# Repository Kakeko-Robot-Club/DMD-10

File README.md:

# DMD-10
ディスクリート部品によるDCブラシモータドライバ
## 目次
 - [仕様](#仕様)
 - [変更履歴](#変更履歴)
 - [発注](#発注)
 - [部品実装](#部品実装)
 - [使い方](#使い方)
## 仕様
### 絶対最大定格
| 項目                  | 記号            | Max      | 単位 | 
| --------------------- | :-------------: | :------: | :--: | 
| モータ出力電流(rms)   | I<sub>OUT</sub>      | 10       | A    | 
| モータ出力電流(peak)  | I<sub>OUT_PEAK</sub> | 17       | A    | 
| モータ電源電圧        | V<sub>DD</sub>       | 0~16     | V    | 
| ロジック入力電圧      | V<sub>IN</sub>       | -6~23    | V    | 
| 保存温度             | T<sub>S</sub>      | -55~125   | ℃   | 
### 電気的特性・動作範囲
| 項目                  | 記号            | Min | Typ. | Max | 単位 | コンディション    | 
| --------------------- | :-------------: | :-: | :--: | :-: | :--: | ----------------- | 
| モータ電源電圧        | V<sub>DD</sub>  | 6   | -    | 16  | V    |                   | 
| ロジック入力電圧(High)| V<sub>IH</sub>  | 3.6 | -    | 20  | V    |                   | 
| ロジック入力電圧(Low) | V<sub>IL</sub>  | 0   | -    | 1.4 | V    |                   | 
| ロジックPWM周波数    | f<sub>IN</sub>  | -   | -    | 27  | kHz    |                   | 
| ロジック入力電流      | I<sub>IN</sub>  | -   | 10   | -   | mA   | V<sub>IN</sub>=5V | 
### その他
| 項目                  | 記号            | Min | Typ. | Max | 単位 | 備考              | 
| --------------------- | :-------------: | :-: | :--: | :-: | :--: | ----------------- | 
| 基板サイズ(縦)        |                 | -   | 55   | -   | mm   |                   | 
| 基板サイズ(横)        |                 | -   | 60   | -   | mm   |                   | 
| 取り付け穴サイズ      |                 | -   | 3.2  | -   | mm   | M3ネジ用          | 
| 取り付け穴ピッチ(縦)  |                 | -   | 46   | -   | mm   |                   | 
| 取り付け穴ピッチ(横)  |                 | -   | 35   | -   | mm   |                   | 
### 図
 - [回路図](https://github.com/Kakeko-Robot-Club/DMD-10/blob/main/preview/schematic.pdf)
 - [基板外形図](https://github.com/Kakeko-Robot-Club/DMD-10/blob/main/preview/pcb.pdf)
## 変更履歴
 - Rev. A
	 - 初版(GitHubには未掲載)
 - Rev. B
	 - 部品リファレンス番号の振り直し
## 発注
 - 発注手順は[Elecrow](https://www.elecrow.com/pcb-manufacturing.html)に発注する際の手順を示しているため、その他の業者に発注する際は各業者の指示に従うこと。
 - 下の1～4の手順が難しい場合、このリポジトリの中にあるgerberフォルダの中のファイルを使用しても良い。ただし、手順1が行えないため注意。
 - 設定はKiCad v5系を元にしているため、その他のバージョンの場合は同等の設定にすること。
1. KiCadのPcbnewを用いて基板型番の下にある週番号を振り直す。
	 - この手順は省略できるが、製造時期を明確にするために行ったほうが良い。
2. Pcbnewから、ファイル→プロットと進み、出てきた画面で次のように設定をし、「製造ファイル出力」を押す。
	 - 出力フォーマット: ガーバー
	 - 出力ディレクトリ: gerberなど分かりやすいもの
	 - 含まれるレイヤ
		 - [x] F.Cu
		 - [x] B.Cu
		 - [x] F.SilkS
		 - [x] B.SilkS
		 - [x] F.Mask
		 - [x] B.Mask
		 - [x] Edge.Cuts
		 - その他はチェックを外す
	 - 全般オプション
		 - [x] フットプリントの定数をプロット
		 - [x] フットプリントのリファレンスをプロット
		 - [x] 基板外形レイヤーのデータを他のレイヤーから除外
		 - [x] シルクからパッドを除外
		 - その他はチェックを外す
		 - デフォルトの線幅: 0.1mm
	 - ガーバーオプション
		 - [x] Protelの拡張子を使用
		 - [x] シルクをレジストで抜く
		 - [x] ネットリスト属性を含む
		 - その他はチェックを外す
		 - 座標フォーマット: 4.6, 単位 mm
3. 製造ファイル出力ボタンの右の方にある、「ドリルファイルを生成...」ボタンから、次のように設定し、「ドリルファイルを生成」を押す。
	 - 出力フォルダ: 製造ファイル出力で設定したものと同じもの
	 - ドリルファイルフォーマット: Excellon
		 - チェックはすべて外す
		 - 長円穴ドリルモードは「routeコマンドを使用」にチェック
	 - マップファイルフォーマット: ガーバー
	 - ドリル原点: 絶対位置
	 - ドリル単位: mm
	 - ゼロの扱い: 後方ゼロ省略
4. 基板プロジェクトフォルダの中のフォルダ、または自分で設定したフォルダの中に生成したファイル群があるので、次のようにリネームする。
	 - DMD-10-Edge.Cuts.gm1のみ、拡張子がgmlに変わっているため注意

	| 元ファイル名         | リネーム後      | 
	| -------------------- | --------------- | 
	| DMD-10-B.Cu.gbl      | DMD-10.gbl      | 
	| DMD-10-B.Mask.gbs    | DMD-10.gbs      | 
	| DMD-10-B.SilkS.gbo   | DMD-10.gbo      | 
	| DMD-10-Edge.Cuts.gm1 | DMD-10.gml      | 
	| DMD-10-F.Cu.gtl      | DMD-10.gtl      | 
	| DMD-10-F.Mask.gts    | DMD-10.gts      | 
	| DMD-10-F.SilkS.gto   | DMD-10.gto      | 
	| DMD-10-NPTH.drl      | DMD-10-NPTH.txt | 
	| DMD-10-PTH.drl       | DMD-10-PTH.txt  | 
5. ファイルをZIPファイルに圧縮する。
6. [Elecrow](https://www.elecrow.com/pcb-manufacturing.html)にZIPファイルをアップロードし、次のような設定で発注する。
	 - Elecrowにログインしておくこと。

	| 項目                 | 設定             | 備考                                                   | 
	| -------------------- | :--------------: | ------------------------------------------------------ | 
	| Layer                | 2 layers         | 変更しないこと。                                       | 
	| Dimensions           | 60 x 55          | 変更しないこと。                                       | 
	| PCB Qty              | 必要枚数を設定   | 10枚までは安い。設定より少し多めに届くことが多い。     | 
	| Different PCB Design | 1                | 変更しないこと。                                       | 
	| PCB Thickness        | 1.6              | 薄くできるが非推奨。厚くすると高くなる。               | 
	| PCB Color            | 基板色を設定     | 一部の色は高い。                                       | 
	| Surface Finish       | HASL             | 鉛フリーや金メッキなども指定できるが高くなる。         | 
	| Castellated Hole     | No               | 変更しないこと。                                       | 
	| Copper Weight        | 1oz              | 2ozは基板銅箔が厚くなるが高くなる。                    | 
	| PCB Stencil          | No               | ステンシルは表面実装部品のリフロー半田に使うので不要。 | 
	| Production Time      | 4-7 working days | Rushなどにしてもそこまで早くならない。                 | 
	| Country              | Japan            | 配送先の国なので日本を選択。                           | 
	| Shipping Cost        | Sagawa           | 一番安いものを選んでおけばよい。                       | 
## 部品実装
 - 部品リスト
	| リファレンス | 部品                | 秋月電子                                                                                                                        | 代替品情報                                              | 
	| ------------ | ------------------- | ------------------------------------------------------------------------------------------------------------------------------- | ------------------------------------------------------- | 
	| D1～D4       | SBM1045VSS          | [I-15642](https://akizukidenshi.com/catalog/g/gI-15642/)                                                                        | I<sub>F</sub>>10A, V<sub>R</sub>>16V                    | 
	| J1～J4       | PCB-20(632F)        | [C-05115](https://akizukidenshi.com/catalog/g/gC-05115/)                                                                        | 15A以上流せるもの, できるだけ金属面積が広いもの         | 
	| J5           | PH-1x40RG(2)        | [C-01627](https://akizukidenshi.com/catalog/g/gC-01627/)                                                                        | 2.54mmピッチ, L字                                       | 
	| Q1, Q2       | MTA100N10KRI3       | 1個: [I-15846](https://akizukidenshi.com/catalog/g/gI-15846/)<br>10個: [I-15847](https://akizukidenshi.com/catalog/g/gI-15847/) | TO-251, Nch, I<sub>D</sub>>2A, V<sub>GS(th)</sub><4V    | 
	| Q3, Q5       | IRFU5505PBF         | [I-06021](https://akizukidenshi.com/catalog/g/gI-06021/)                                                                        | TO-251, Pch, I<sub>D</sub><-15A, V<sub>GS(th)</sub>>-4V | 
	| Q4, Q6       | IRLU3410PBF         | [I-06025](https://akizukidenshi.com/catalog/g/gI-06025/)                                                                        | TO-251, Nch, I<sub>D</sub>>15A, V<sub>GS(th)</sub><4V   | 
	| R1～R4       | 300Ωカーボン抵抗   | [R-07811](https://akizukidenshi.com/catalog/g/gR-07811/)                                                                        |                                                         | 
	| R5, R6       | 10kΩカーボン抵抗   | [R-07838](https://akizukidenshi.com/catalog/g/gR-07838/)                                                                        |                                                         | 
	| R7～R10      | 10Ωカーボン抵抗    | [R-07795](https://akizukidenshi.com/catalog/g/gR-07795/)                                                                        |                                                         | 
	| RN1          | 1kΩ 4素子集合抵抗  | [R-14225](https://akizukidenshi.com/catalog/g/gR-14225/)                                                                        |                                                         | 
	| RN2          | 10kΩ 4素子集合抵抗 | [R-11909](https://akizukidenshi.com/catalog/g/gR-11909/)                                                                        |                                                         | 
	| U1, U2       | UPC817CG-D04-T      | [I-16090](https://akizukidenshi.com/catalog/g/gI-16090/)                                                                        | PC817系フォトカプラ                                     | 
 - 注意点
	 - 抵抗やダイオードは縦取り付けになるよう、リードを曲げること。
	 - リードを曲げた抵抗を取り付ける際、基板から浮かないように取り付けること。
		 - 浮いている場合、抵抗が左右に曲がりやすくなり、ショートの原因になるため注意。
	 - 放熱のため、FETの頭の部分の半田付けは確実に行う。
		 - ランドが広いため、大出力の半田ごてを用いたほうが良い。
	 - ネジ端子はよく温めないと半田が流れないため、やけどに注意。
	 - 言うまでもなく、部品の向き・極性の間違い、定数の間違いに注意する。
## 使い方
1. 次のように接続する。
	| 端子      | リファレンス | 接続先             | 
	| --------- | ------------ | ------------------ | 
	| POWER IN  | J2           | モータ電源プラス   | 
	| POWER GND | J3           | モータ電源マイナス | 
	| MOTOR OUT | J1, J4       | DCブラシモータ     | 
	| IN1       | J5           | マイコン等出力端子 | 
	| IN2       | J5           | マイコン等出力端子 | 
	| GND       | J5           | マイコン等グランド | 
2. マイコン等から次の表に従い、IN1・IN2に信号を出力する。
	| IN2 | IN1 | J4  | J1  | モータ   | 
	| --- | --- | --- | --- | -------- | 
	| 0   | 0   | 1   | 1   | ブレーキ | 
	| 0   | 1   | 1   | 0   | 回転     | 
	| 1   | 0   | 0   | 1   | 逆回転   | 
	| 1   | 1   | 0   | 0   | ブレーキ | 
  
	*IN1・IN2欄は入力状態、J1・J4欄は出力状態、モータ欄は出力状態によるモータの状態を表す。  
	*IN1・IN2については0をV<sub>IL</sub>、1をV<sub>IH</sub>（PWM入力含む）に従うものとする。  
	*J1・J4については0を0V、1をV<sub>DD</sub>に従うものとする。

### 使用上の注意
 - 各端子をショートさせないこと。
 - 熱がこもるような狭い空間で使用しないこと。
 - 定格を超えての使用をしないこと。
 - 異常発熱がある場合は使用しないこと。

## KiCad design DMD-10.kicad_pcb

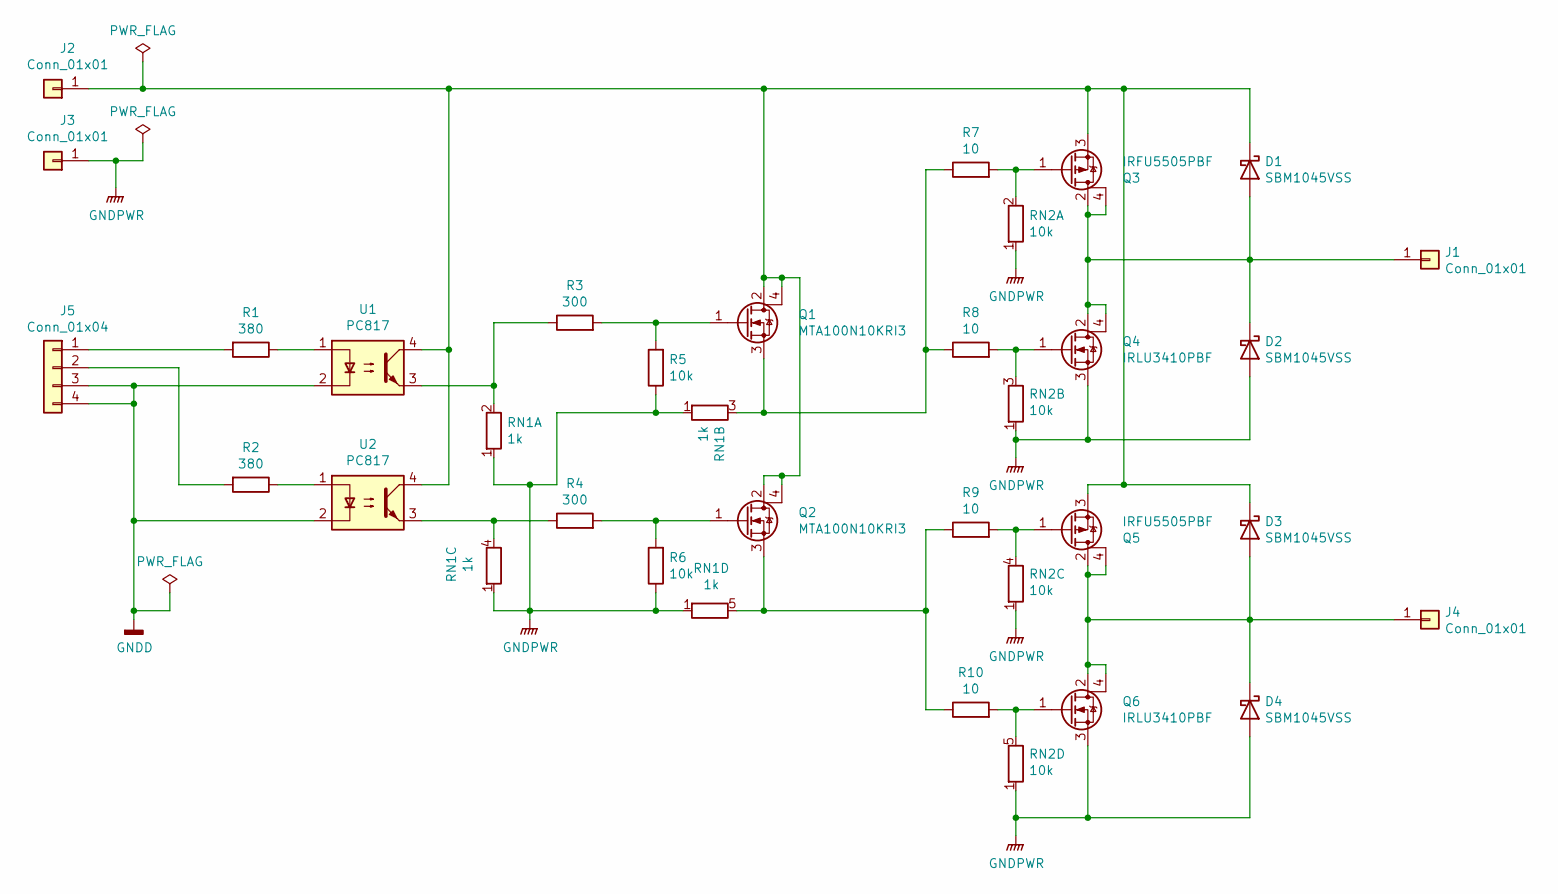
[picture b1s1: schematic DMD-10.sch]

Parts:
D1, D2, D3, D4: SBM1045VSS; D_DO-201AD_P3.81mm_Vertical_AnodeUp
J1, J2, J3, J4: Conn_01x01; DIP-6_W7.62mm
J5: Conn_01x04; PinHeader_1x04_P2.54mm_Horizontal
Q1, Q2: MTA100N10KRI3; TO-251-3-1EP_Horizontal_TabDown
Q3, Q5: IRFU5505PBF; TO-251-3-1EP_Horizontal_TabDown
Q4, Q6: IRLU3410PBF; TO-251-3-1EP_Horizontal_TabDown
R1, R2: 380; R_Axial_DIN0204_L3.6mm_D1.6mm_P2.54mm_Vertical
R3, R4: 300; R_Axial_DIN0204_L3.6mm_D1.6mm_P2.54mm_Vertical
R5, R6: 10k; R_Axial_DIN0204_L3.6mm_D1.6mm_P2.54mm_Vertical
R7, R8, R9, R10: 10; R_Axial_DIN0204_L3.6mm_D1.6mm_P2.54mm_Vertical
RN1: 1k; R_Array_SIP5
RN2: 10k; R_Array_SIP5
U1, U2: PC817; DIP-4_W7.62mm

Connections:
GNDD: J5.3, J5.4, U1.2, U2.2
GNDPWR: D2.2 (A), D4.2 (A), J3.1, Q4.3 (S), Q6.3 (S), R5.1, R6.1, RN1.1 (R1.1), RN2.1 (R1.1)
unnamed: D1.1 (K), D3.1 (K), J2.1, Q1.2 (D), Q1.4 (D), Q2.2 (D), Q2.4 (D), Q3.3 (S), Q5.3 (S), U1.4, U2.4
unnamed: D1.2 (A), D2.1 (K), J1.1, Q3.2 (D), Q3.4 (D), Q4.2 (D), Q4.4 (D)
unnamed: D3.2 (A), D4.1 (K), J4.1, Q5.2 (D), Q5.4 (D), Q6.2 (D), Q6.4 (D)
unnamed: J5.1, R1.2
unnamed: J5.2, R2.2
unnamed: Q1.1 (G), R3.2, R5.2
unnamed: Q1.3 (S), R7.1, R8.1, RN1.3 (R2.2)
unnamed: Q2.1 (G), R4.2, R6.2
unnamed: Q2.3 (S), R9.1, R10.1, RN1.5 (R4.2)
unnamed: Q3.1 (G), R7.2, RN2.2 (R1.2)
unnamed: Q4.1 (G), R8.2, RN2.3 (R2.2)
unnamed: Q5.1 (G), R9.2, RN2.4 (R3.2)
unnamed: Q6.1 (G), R10.2, RN2.5 (R4.2)
unnamed: R1.1, U1.1
unnamed: R2.1, U2.1
unnamed: R3.1, RN1.2 (R1.2), U1.3
unnamed: R4.1, RN1.4 (R3.2), U2.3

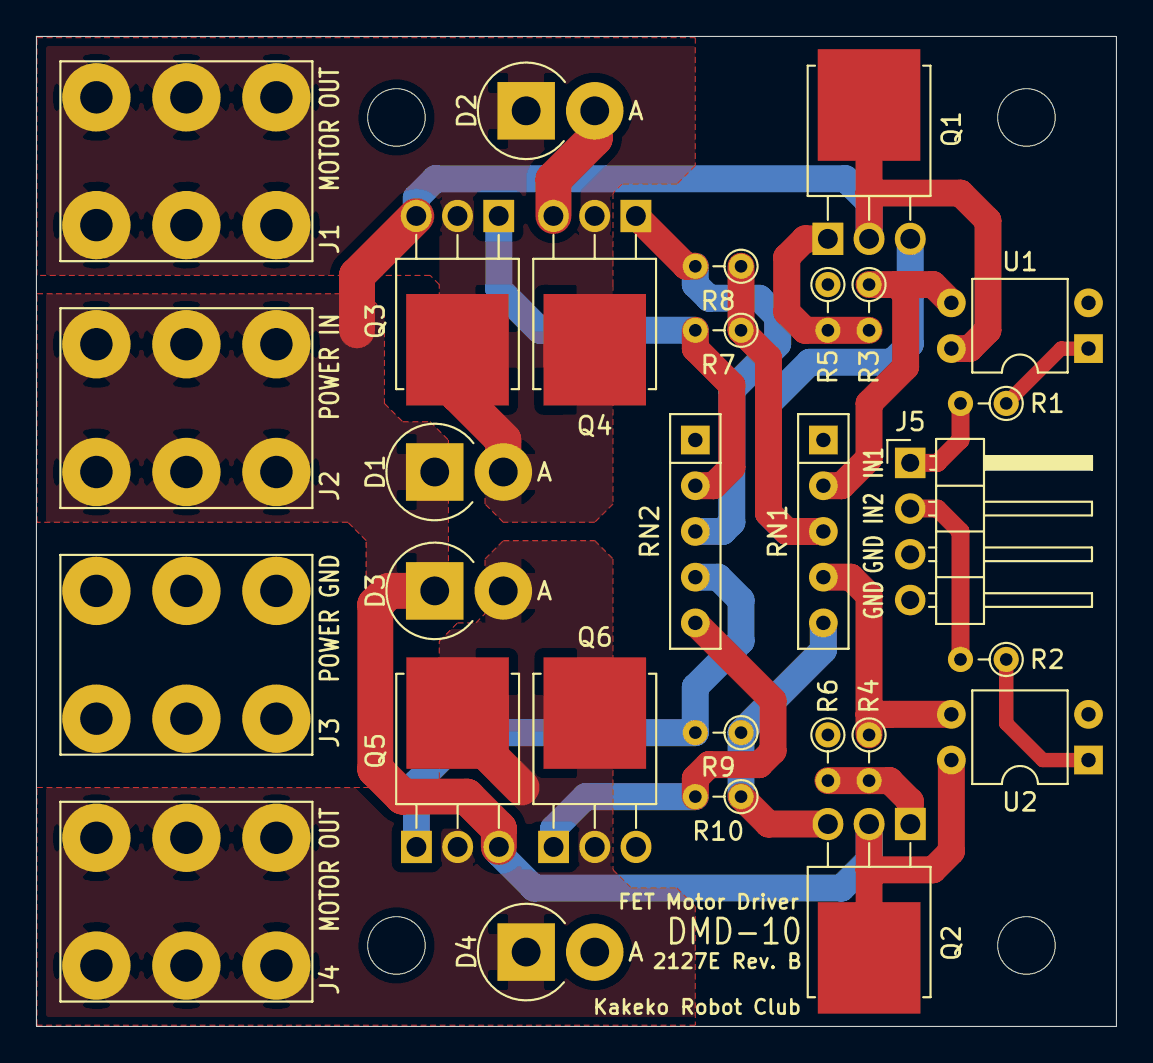
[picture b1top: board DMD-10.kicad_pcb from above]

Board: 2 copper layers, 60.0 x 55.0 mm, 29 parts (0 on the bottom side), 19 nets.

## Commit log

2021-12-05 Add files
